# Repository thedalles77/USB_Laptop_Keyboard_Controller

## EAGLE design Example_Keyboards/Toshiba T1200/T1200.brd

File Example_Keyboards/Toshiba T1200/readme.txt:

I have not tested this code so there may be errors.
The matrix came from a post on Reddit here:
https://www.reddit.com/r/olkb/comments/dk514w/using_existing_laptop_keyboard_from_toshiba_t1200/
The Eagle board files are for a Teensy LC but since it's now obsolete, they should not be used.
I translated the code to a Teensy 4.1 and you can use the 
Easy Soldering board from step 5 of my Instructable. This board will work with a 22 pin 1.25mm pitch FPC connector.
The PDF's describe the original Teensy LC connector board and the keyboard matrix.

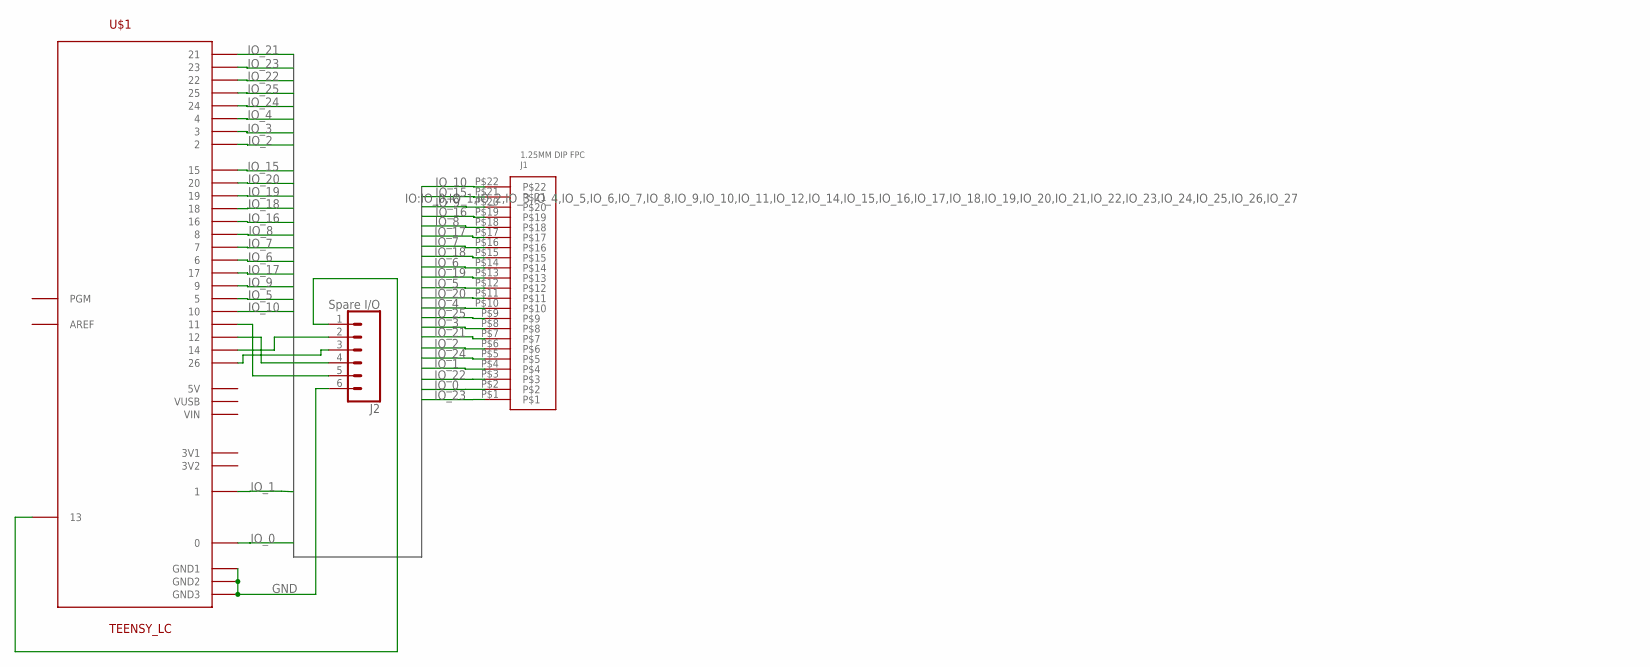
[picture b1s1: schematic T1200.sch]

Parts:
J1: 1.25MM DIP FPC; T1200_CON
J2: Spare I/O; 1X06
U$1: TEENSY_LC

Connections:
GND: J2.6, U$1.GND1, U$1.GND2, U$1.GND3
IO_0: J1.P$2, U$1.0
IO_1: J1.P$4, U$1.1
IO_2: J1.P$6, U$1.2
IO_3: J1.P$8, U$1.3
IO_4: J1.P$10, U$1.4
IO_5: J1.P$12, U$1.5
IO_6: J1.P$14, U$1.6
IO_7: J1.P$16, U$1.7
IO_8: J1.P$18, U$1.8
IO_9: J1.P$20, U$1.9
IO_10: J1.P$22, U$1.10
IO_15: J1.P$21, U$1.15
IO_16: J1.P$19, U$1.16
IO_17: J1.P$17, U$1.17
IO_18: J1.P$15, U$1.18
IO_19: J1.P$13, U$1.19
IO_20: J1.P$11, U$1.20
IO_21: J1.P$7, U$1.21
IO_22: J1.P$3, U$1.22
IO_23: J1.P$1, U$1.23
IO_24: J1.P$5, U$1.24
IO_25: J1.P$9, U$1.25
unnamed: J2.1, U$1.13
unnamed: J2.4, U$1.12
unnamed: J2.3, U$1.26
unnamed: J2.2, U$1.14
unnamed: J2.5, U$1.11

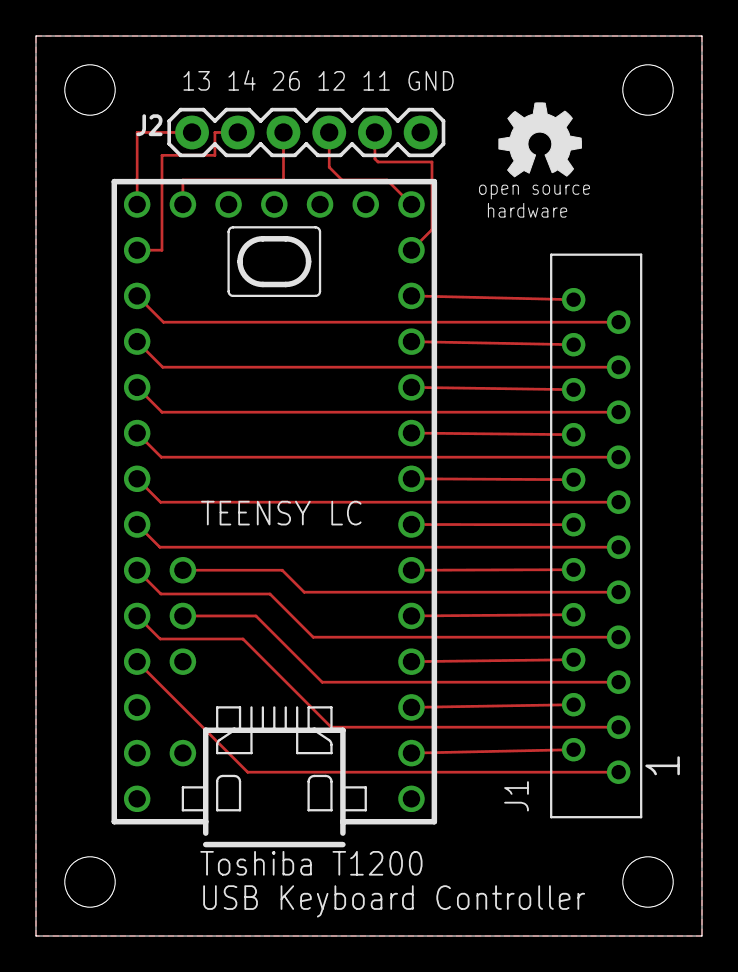
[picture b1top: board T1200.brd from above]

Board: 2 copper layers, 37.0 x 50.0 mm, 4 parts (0 on the bottom side), 28 nets.

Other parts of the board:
U$2: OSHW_5MM

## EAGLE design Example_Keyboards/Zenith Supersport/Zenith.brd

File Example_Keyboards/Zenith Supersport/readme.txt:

This project was originally based on a Teensy LC which is now obsolete.
The code as written will also work with a Teensy 4.0 on the existing LC circuit board with the following changes:
    - Add a flying lead to I/O # 24 on the backside of the Teensy 4.0 that goes to the board at the plated thru hole that was for I/O # 24 on the Teensy LC.
    - Use 150 ohm resistors for the LEDs instead of 75 ohm to stay below the 10ma current capability of the Teensy 4.0 I/O pins.

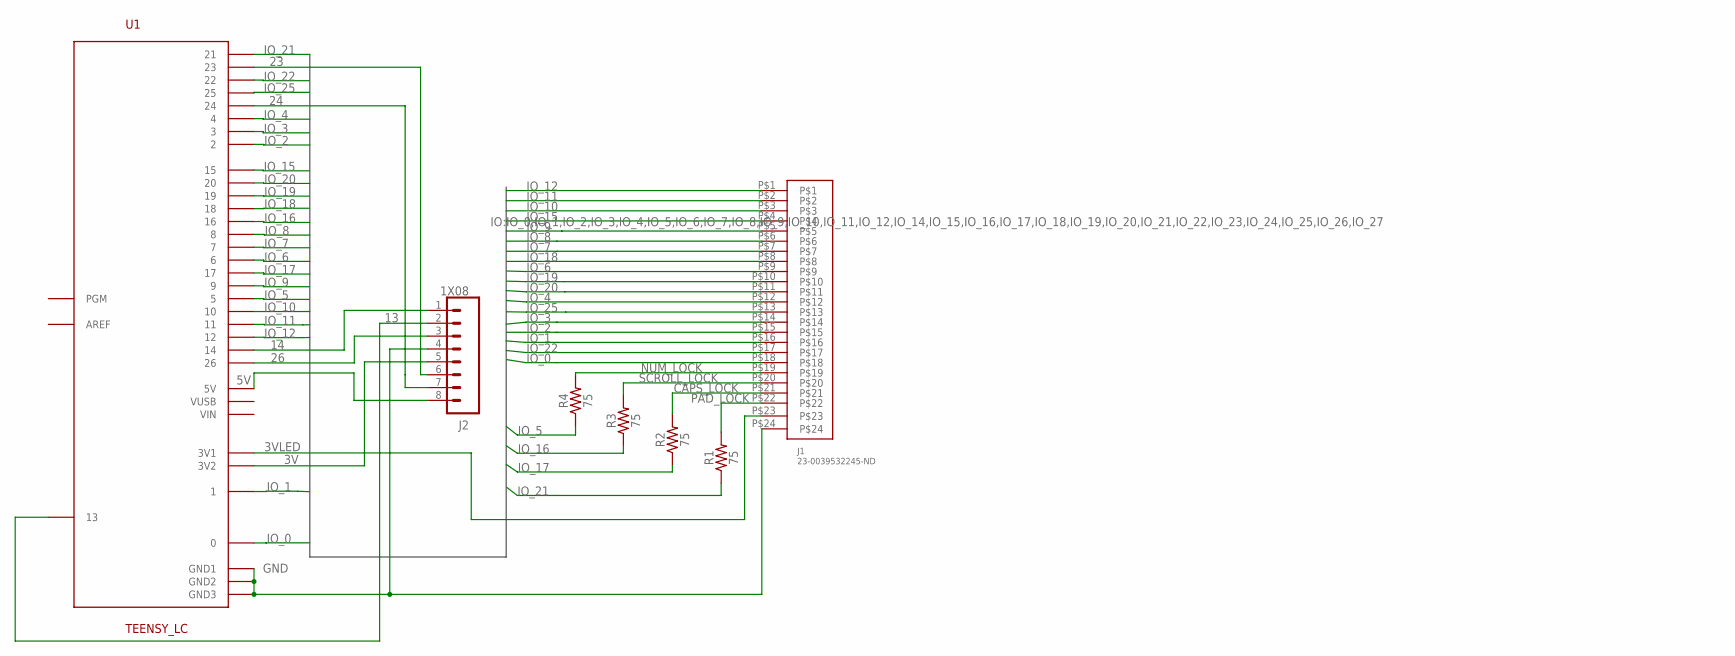
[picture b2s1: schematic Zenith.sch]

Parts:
J1: 23-0039532245-ND; ZENITH_CON
J2: 1X08
R1, R2, R3, R4: 75; AXIAL-0.3
U1: TEENSY_LC

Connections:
3V: J2.5, U1.3V2
3VLED: J1.P$23, U1.3V1
5V: J2.8, U1.5V
13: J2.2, U1.13
14: J2.1, U1.14
23: J2.6, U1.23
24: J2.7, U1.24
26: J2.3, U1.26
CAPS_LOCK: J1.P$21, R2.P$2 (2)
GND: J1.P$24, J2.4, U1.GND1, U1.GND2, U1.GND3
IO_0: J1.P$18, U1.0
IO_1: J1.P$16, U1.1
IO_2: J1.P$15, U1.2
IO_3: J1.P$14, U1.3
IO_4: J1.P$12, U1.4
IO_5: R4.P$1 (1), U1.5
IO_6: J1.P$9, U1.6
IO_7: J1.P$7, U1.7
IO_8: J1.P$6, U1.8
IO_9: J1.P$5, U1.9
IO_10: J1.P$3, U1.10
IO_11: J1.P$2, U1.11
IO_12: J1.P$1, U1.12
IO_15: J1.P$4, U1.15
IO_16: R3.P$1 (1), U1.16
IO_17: R2.P$1 (1), U1.17
IO_18: J1.P$8, U1.18
IO_19: J1.P$10, U1.19
IO_20: J1.P$11, U1.20
IO_21: R1.P$1 (1), U1.21
IO_22: J1.P$17, U1.22
IO_25: J1.P$13, U1.25
NUM_LOCK: J1.P$19, R4.P$2 (2)
PAD_LOCK: J1.P$22, R1.P$2 (2)
SCROLL_LOCK: J1.P$20, R3.P$2 (2)

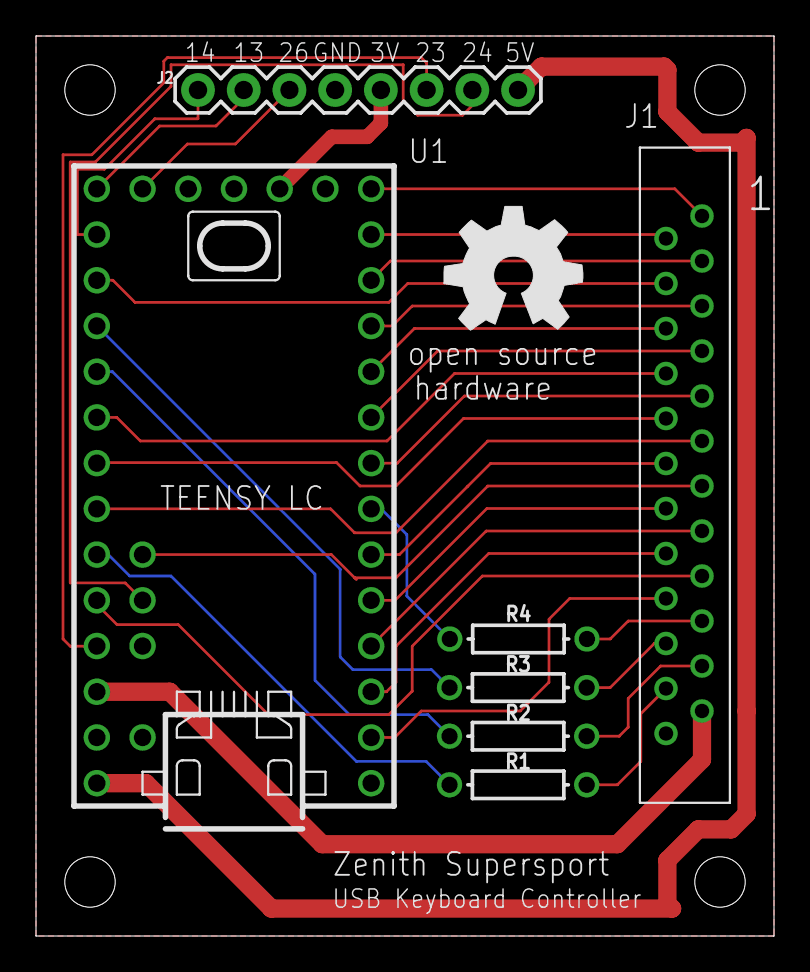
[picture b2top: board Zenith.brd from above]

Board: 2 copper layers, 41.0 x 50.0 mm, 8 parts (0 on the bottom side), 35 nets.

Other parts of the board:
U$2: OSHW_8MM

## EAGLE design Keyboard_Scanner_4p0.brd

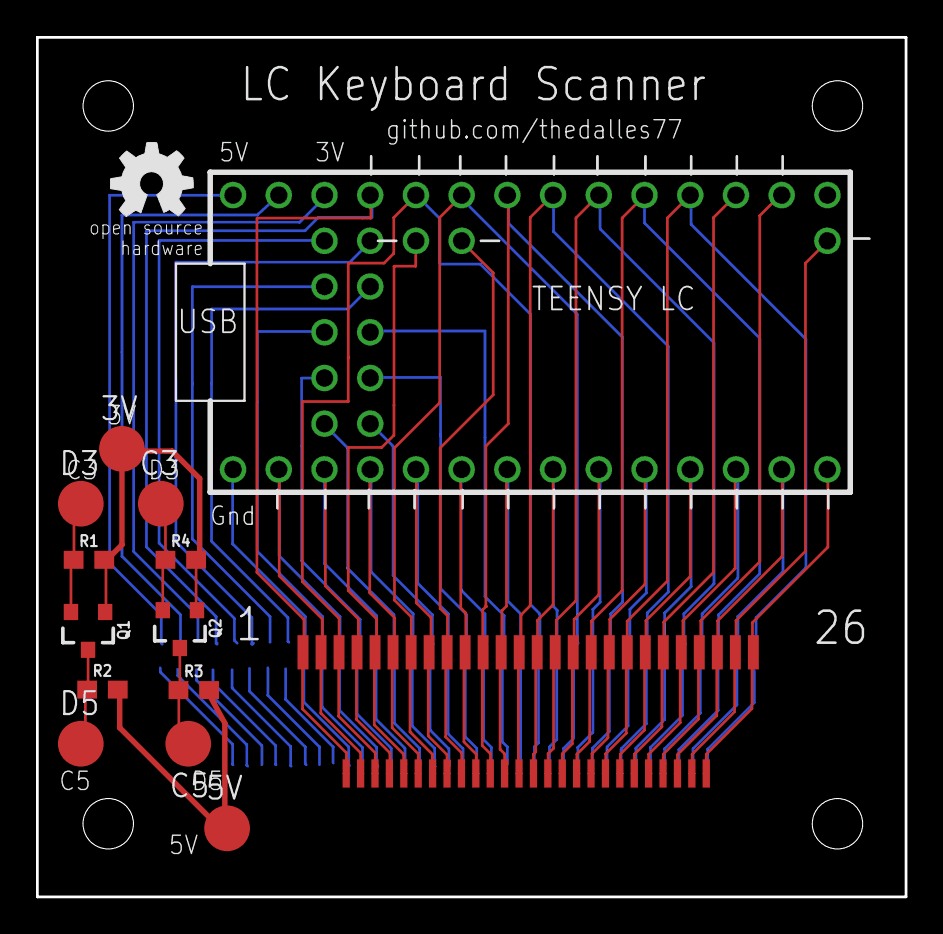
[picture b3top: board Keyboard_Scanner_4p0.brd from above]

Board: 2 copper layers, 48.3 x 47.8 mm, 16 parts (0 on the bottom side), 4 nets.

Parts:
3V, 5V: B2,54
C3, C5: B2,54
D3, D5: B2,54
E$1: TEENSY_COMBO_4P0
E$2: FPC_DUAL
E$3: FPC_DUAL_FRONT
E$4: OSHW_5MM
Q1, Q2: 220mA/50V/3.5Ω; SOT23-3
R1, R2, R3, R4: 10k; 0603

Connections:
CLK: Q1.2, R1.1
DATA: Q2.2, R4.1
TP_CLK: Q1.3, R2.1
TP_DATA: Q2.3, R3.1

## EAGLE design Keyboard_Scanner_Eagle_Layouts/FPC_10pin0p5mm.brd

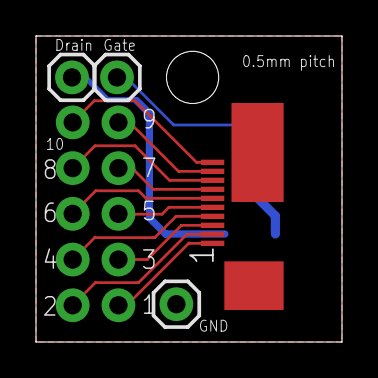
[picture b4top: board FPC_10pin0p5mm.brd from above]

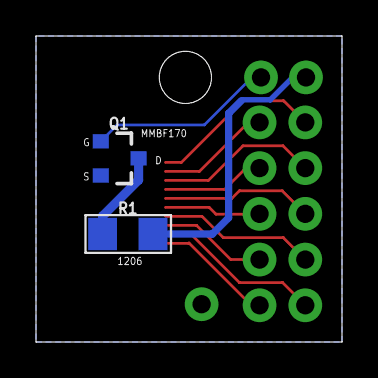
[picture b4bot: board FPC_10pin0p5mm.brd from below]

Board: 2 copper layers, 17.0 x 17.0 mm, 7 parts (2 on the bottom side), 14 nets.

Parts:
J1: J1; KYOCERA046288
J2: J2; 2X5_NOSILK
J3: J3; 1X01
J4: J4; 1X01
J5: J5; 1X01
Q1: MMBF170
R1: 1206; R1206

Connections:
GND: J1.P$11, J1.P$12, J5.1, Q1.2
unnamed: J1.P$1, J2.1
unnamed: J1.P$2, J2.2
unnamed: J1.P$3, J2.3
unnamed: J1.P$4, J2.4
unnamed: J1.P$5, J2.5
unnamed: J1.P$6, J2.6
unnamed: J1.P$7, J2.7
unnamed: J1.P$8, J2.8
unnamed: J1.P$9, J2.9
unnamed: J1.P$10, J2.10
unnamed: Q1.3, R1.1
unnamed: J3.1, R1.2
unnamed: J4.1, Q1.1

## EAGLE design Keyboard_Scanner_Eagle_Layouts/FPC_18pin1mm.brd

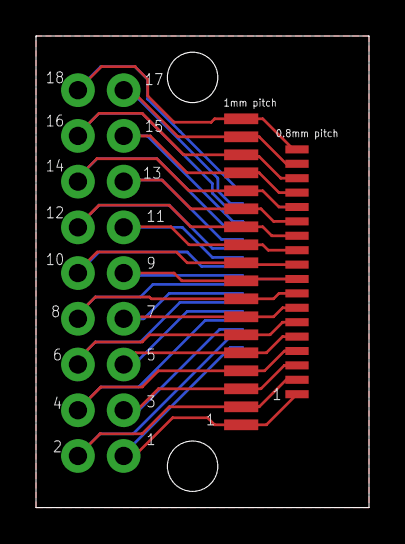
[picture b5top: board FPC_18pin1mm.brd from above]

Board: 2 copper layers, 18.5 x 26.2 mm, 4 parts (1 on the bottom side), 18 nets.

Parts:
J1: 522711879
J2: CONN_18X2
J3: 18PIN0P8MM
J4: 18PIN0P5MM

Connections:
unnamed: J1.P$18, J2.18, J3.P$18, J4.P$1
unnamed: J1.P$17, J2.17, J3.P$17, J4.P$2
unnamed: J1.P$16, J2.16, J3.P$16, J4.P$3
unnamed: J1.P$15, J2.15, J3.P$15, J4.P$4
unnamed: J1.P$14, J2.14, J3.P$14, J4.P$5
unnamed: J1.P$13, J2.13, J3.P$13, J4.P$6
unnamed: J1.P$12, J2.12, J3.P$12, J4.P$7
unnamed: J1.P$11, J2.11, J3.P$11, J4.P$8
unnamed: J1.P$10, J2.10, J3.P$10, J4.P$9
unnamed: J1.P$9, J2.9, J3.P$9, J4.P$10
unnamed: J1.P$8, J2.8, J3.P$8, J4.P$11
unnamed: J1.P$7, J2.7, J3.P$7, J4.P$12
unnamed: J1.P$6, J2.6, J3.P$6, J4.P$13
unnamed: J1.P$5, J2.5, J3.P$5, J4.P$14
unnamed: J1.P$4, J2.4, J3.P$4, J4.P$15
unnamed: J1.P$3, J2.3, J3.P$3, J4.P$16
unnamed: J1.P$2, J2.2, J3.P$2, J4.P$17
unnamed: J1.P$1, J2.1, J3.P$1, J4.P$18

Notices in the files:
parts and their libraries:
SparkFun-Connectors: Licensing: Creative Commons ShareAlike 4.0 International - https://creativecommons.org/licenses/by-sa/4.0
